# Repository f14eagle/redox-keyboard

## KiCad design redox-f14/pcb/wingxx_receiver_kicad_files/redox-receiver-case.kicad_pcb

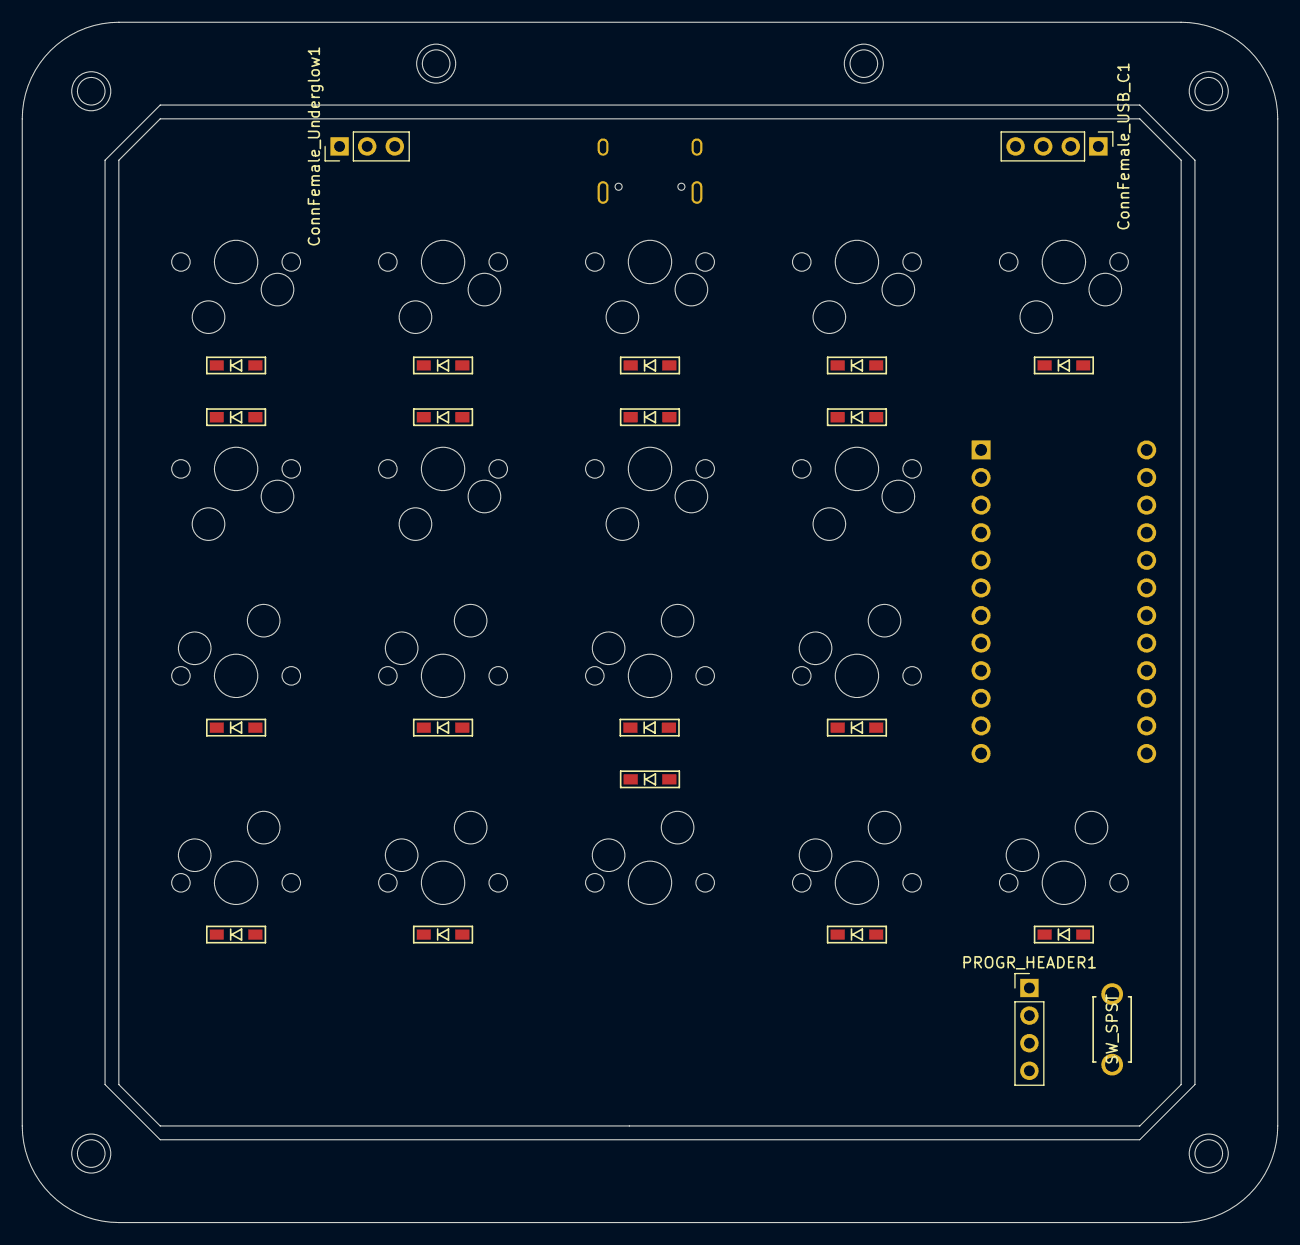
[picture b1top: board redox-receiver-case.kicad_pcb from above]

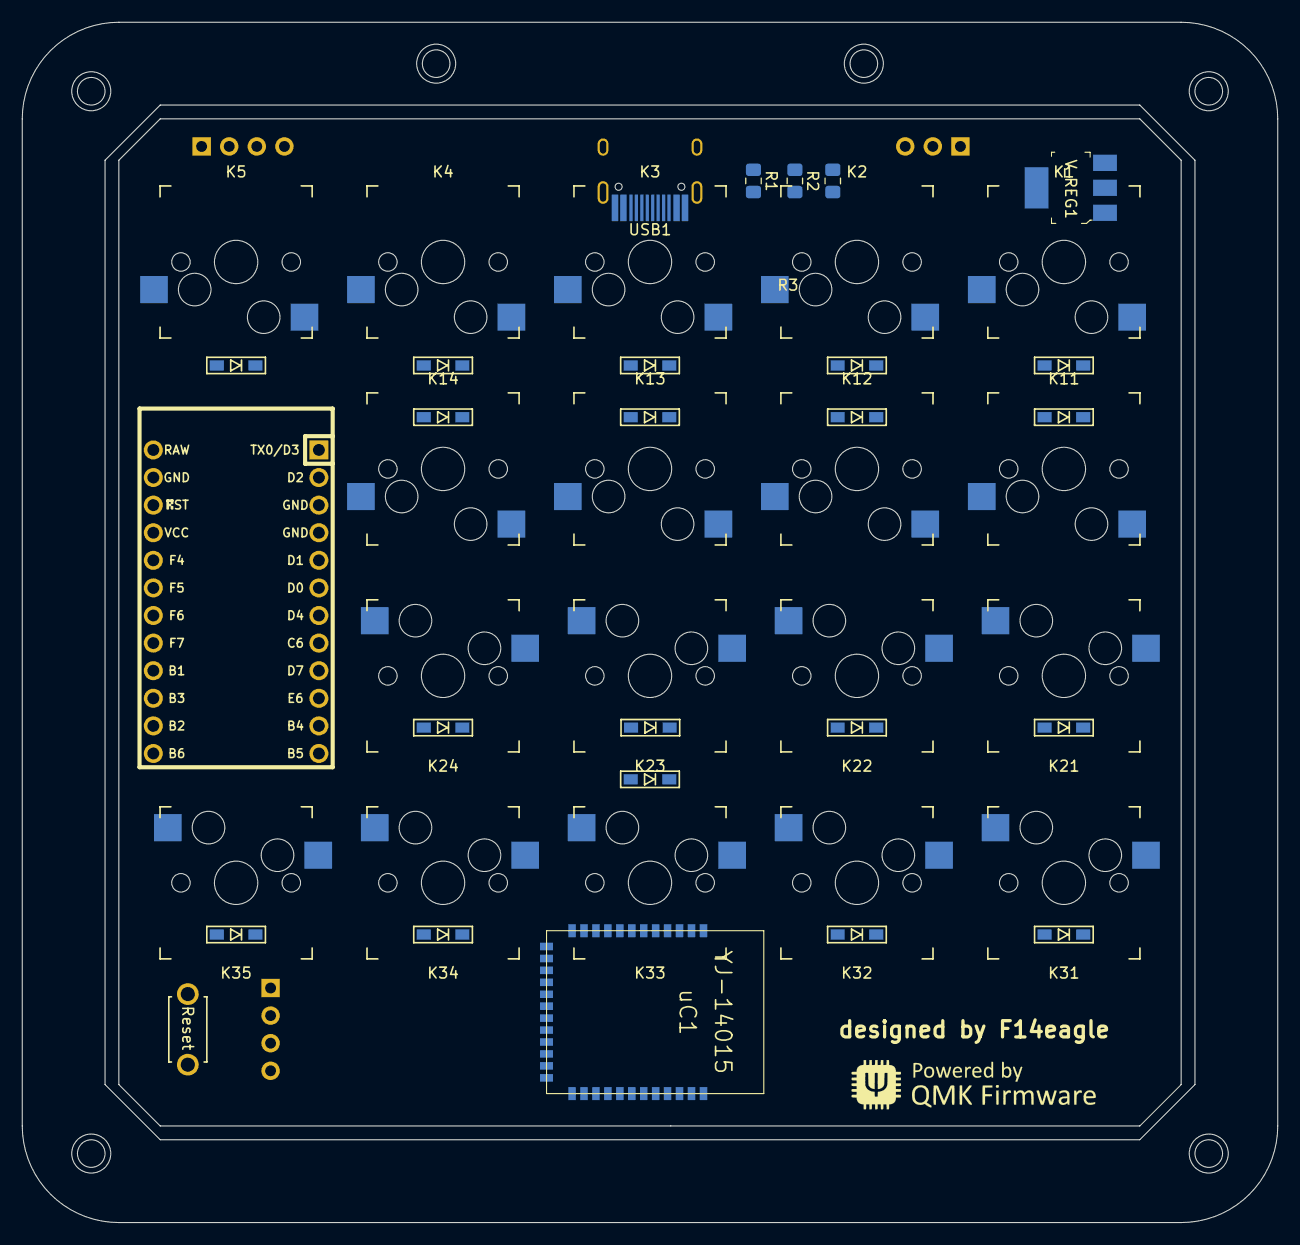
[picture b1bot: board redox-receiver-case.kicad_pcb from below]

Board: 2 copper layers, 115.6 x 110.5 mm, 47 parts (6 on the bottom side), 41 nets, no tracks yet.

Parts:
ConnFemale_USB_C1: Conn_01x04_Female; PinHeader_1x04_P2.54mm_Vertical
ConnFemale_Underglow1: Conn_01x03_Female; PinHeader_1x03_P2.54mm_Vertical
D1, D2, D3, D4, D5, D11, D12, D13, D14, D21, D22, D23, D24, D31, D32, D33, D34, D35: D; D3_SMD
K1, K2, K3, K4, K5, K11, K12, K13, K14, K21, K22, K23, K24, K31, K32, K33, K34, K35: KEYSW-redox_rev1-rescue; Kailh_socket
PROGR_HEADER1: Conn_01x04_Female; PinHeader_1x04_P2.54mm_Vertical
R1, R2, R3: R; R_0805_2012Metric_Pad1.15x1.40mm_HandSolder
RESET1: SW_SPST; ResetSW
U1: Pro_Micro; ArduinoProMicro
USB1: HRO-TYPE-C-31-M-12; HRO-TYPE-C-31-M-12-HandSoldering
V_REG1: LD1117S33CTR; SOT-223
uC1: YJ-14015; MY-YJ-14015-Module

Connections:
C_D+: ConnFemale_USB_C1.3, USB1.6, USB1.8
C_D-: ConnFemale_USB_C1.2, USB1.5, USB1.7
C_GND: ConnFemale_USB_C1.4, USB1.1, USB1.12
C_VCC: ConnFemale_USB_C1.1, USB1.2, USB1.11
GND: ConnFemale_Underglow1.3, PROGR_HEADER1.2, R2.2, RESET1.2, U1.3, U1.4, U1.23, V_REG1.1, uC1.1, uC1.11
unnamed: D1.2, K1.2
unnamed: D2.2, K2.2
unnamed: D3.2, K3.2
unnamed: D4.2, K4.2
unnamed: D5.2, K5.2
unnamed: D11.2, K11.2
unnamed: D12.2, K12.2
unnamed: D13.2, K13.2
unnamed: D14.2, K14.2
unnamed: D21.2, K21.2
unnamed: D22.2, K22.2
unnamed: D23.2, K23.2
unnamed: D24.2, K24.2
unnamed: D31.2, K31.2
unnamed: D32.2, K32.2
unnamed: D33.2, K33.2
unnamed: D34.2, K34.2
unnamed: D35.2, K35.2
RGB_DATA: ConnFemale_Underglow1.2, U1.12
RST: RESET1.1, U1.22
RXI: U1.2, uC1.5
SWCLK: PROGR_HEADER1.4, uC1.32
SWDIO: PROGR_HEADER1.3, uC1.31
TXO: R1.1, R3.1, U1.1
TXODIV: R1.2, R2.1, R3.2, uC1.6
VCC: PROGR_HEADER1.1, V_REG1.2, V_REG1.4, uC1.12
VIN: ConnFemale_Underglow1.1, U1.24, V_REG1.3
col0: K1.1, K11.1, K21.1, K31.1, U1.18
col1: K2.1, K12.1, K22.1, K32.1, U1.17
col2: K3.1, K13.1, K23.1, K33.1, U1.16
col3: K4.1, K14.1, K24.1, K34.1, U1.15
col4: K5.1, K35.1, U1.14
row0: D1.1, D2.1, D3.1, D4.1, D5.1, U1.7
row1: D11.1, D12.1, D13.1, D14.1, U1.8
row2: D21.1, D22.1, D23.1, D24.1, U1.9
row3: D31.1, D32.1, D33.1, D34.1, D35.1, U1.10
